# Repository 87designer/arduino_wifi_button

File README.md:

<!-- PROJECT LOGO -->
<br />
<div align="center">

  <p align="center">
    <br />
    <!-- <a href="https://github.com/87designer/arduino_infant_tracker"><strong>Explore the docs »</strong></a>
    <br />
    <br />
    <a href="https://github.com/87designer/arduino_infant_tracker">View Demo</a> -->
  </p>
</div>

<!-- TABLE OF CONTENTS -->
<details>
  <summary>Table of Contents</summary>
  <ol>
    <li>
      <a href="#about-the-project">About The Project</a>
      <ul>
        <li><a href="#built-with">Built With</a></li>
      </ul>
    </li>
    <li>
      <a href="#getting-started">Getting Started</a>
      <ul>
        <li><a href="#prerequisites">Prerequisites</a></li>
        <li><a href="#installation">Installation</a></li>
      </ul>
    </li>
    <li><a href="#usage">Usage</a></li>
    <li><a href="#roadmap">Roadmap</a></li>
    <li><a href="#acknowledgments">Acknowledgments</a></li>
  </ol>
</details>

<!-- ABOUT THE PROJECT -->
## About The Project

After being introduced to Arduino and electronics through the "30 Days Lost in Space" Adventure Kit from Inventr, I was served a social media ad for a small consumer button device that logged events to a dashboard, via wifi. Seeing how I could potentially leverage a device like this in my day to day, my gears got to turning.

```
Arduino + New Electronic Skills = I can make that
```

And with that, the AWB0412 categorical data logging wifi button was born. *(as an Arduino Uno Shield)*

When the device is powered on the LED in the top left will be red. After successful network connectino has been made, the LED will turn Green. When a Button is pressed the LED will blink blue.

There are 4 buttons on the shield giving the ability to log up to 12 different types of events using the methods of single click, double click, & hold +1 second for each button.

<br>
<hr>

#### 3D Model with Components *(Designed using KiCad)*

<div style="display:flex">
     <div style="flex:1;padding-right:10px;">
          
     </div>
     <div style="flex:1;padding-left:10px;">
          
     </div>
</div>

<br>
<hr>

#### PCB *(Vendor Mockup from Gerber files)*

<div style="display:flex">
     <div style="flex:1;padding-right:10px;">
          
     </div>
</div>

<p align="right">(<a href="#readme-top">back to top</a>)</p>

### Built With

* [![Arduino][Arduino]][Arduino-url]
* [![C++][Cplusplus]][Cplusplus-url]
* [![Kicad][KiCad]][KiCad-url]
* [![Google Sheets][googlesheets]][googlesheets-url]
* [![Google Apps Script][appsscript]][appsscript-url]

<p align="right">(<a href="#readme-top">back to top</a>)</p>

<!-- GETTING STARTED -->
## Getting Started

### Prerequisites

1) Install the [Arudino IDE](https://www.arduino.cc/en/software) on your computer
2) Install appropriate [Drivers](https://inventr.io/drivers/) for the Hero board
3) Install [ESP Libraries](https://github.com/esp8266/Arduino)
4) [Configure Cloud](https://www.youtube.com/watch?v=fS0GeaOkNRw) storage and app
    - Setup a Google Sheet to accept the timestamps and categories.
    - Deploy Google Apps Script code to listen for category request and write it to the google sheet.

### Materials:
  * 1 x [Arduino Hero](https://github.com/inventrkits/HERO)
  * 1 x A-Male to B-Male USB Cable
  * 1 x [ESP8266](https://en.wikipedia.org/wiki/ESP8266) ESP-01 Wifi Module
  * 1 x AWB-0412 Arduino Uno Shield PCB
  * 1 x Pin Headers (1x10)
  * 2 x Pin Headers (1x08)
  * 1 x Pin Headers (1x06)
  * 4 x 10ohm Resistor
  * 3 x 220ohm Resistor
  * 1 x RGB LED
  * 4 x 12mm Tactile Button
  * 1 x [EG1271](https://www.digikey.com/en/products/detail/e-switch/EG1271/251335) DPDT Switch Slide
  * 1 x [78B02ST](https://www.digikey.com/en/products/detail/grayhill-inc/78B02ST/726238) DIP Switch Slide

### Installation

<!-- Write about install/uploading the code for hero & wifi module-->

After construction of the Shield is complete, mount the shield to the Arduino and connect to your computer using the compatible USB cable to power on.

1. Open up the Arduino IDE and ensure the correct Board and Port are selected.
2. With all switches on the shield in the operating position, upload a [blank sketch]() to the Arduino.
3. Power down / disconnect the USB cable and slide DPDT switch and top DIP switch *(this will enable programming mode for the wifi module when powered is restored)*.
5. Reconnect the USB and change the board assignment in the IDE to the ESP8266 wifi module *(the port should be the same so ensure it is still assigned)*
6. Upload the [wifi sketch]() to the ESP8266.
7. Once the sketch is finished uploading, slide the top DIP switch on and off to reset the wifi module.
8. Power down / disconnect the USB cable and return all switches to operating position.
9. Reconnect the USB and change the board assignment in the IDE back to the Arduino.
10. Upload the [button sketch]() to the Arduino.
11. Once the sketch is finished uploading, power down / disconnect the USB cable from the computer and the device is ready to operate from an appropriate power source (battery, wall plug, usb cable.)

<p align="right">(<a href="#readme-top">back to top</a>)</p>

<!-- USAGE EXAMPLES -->
## Usage

#### Infant Tracker

One usage example of the AWB0412 wifi button shield would be as an Infant Tracker to help sleep deprived parents keep track of diapers, feedings, sleep schedule etc.

<p align="right">(<a href="#readme-top">back to top</a>)</p>

<!-- ROADMAP -->
## Roadmap

- [x] Breadboard Prototype to test functionality<br>
  
- [x] Document Prototype in hobby CAD software (Tinkercad / Fritzing)<br>
  
- [x] Electronic Design Automation (EDA), and 
    - [x] Schematic Capture<br>
      
    - [x] PCB Layout with Gerber output<br>
      <div style="display:flex">
        <div style="flex:1;padding-right:10px;">
          
        </div>
        <div style="flex:1;padding-right:10px;">
          
        </div>
      </div>
- [ ] Develop Final button commands
- [ ] Develop Method of Powering Device
- [ ] Draft Documentation
- [ ] Assemble Shield & Test Hardware
- [ ] Finalize Documentation
- [ ] Design / Fabricate a Housing possibly 3D printed model

<p align="right">(<a href="#readme-top">back to top</a>)</p>

<!-- ACKNOWLEDGMENTS -->
## Acknowledgments

* Special shoutout to the [Inventr](https://inventr.io/) Adventure Kit for laying the foundation for electronics that helped bring this project to life.
* [LogMaker360](https://www.youtube.com/watch?v=fS0GeaOkNRw) Youtube video walkthrough on how to get arduino to write to google sheets.
* [Electronics Hub](https://www.electronicshub.org/esp8266-arduino-interface/) Great article with detailed information regarding the ESP8266 ESP-01
* [Gerber/Drill File Generation Guide](https://support.jlcpcb.com/article/194-how-to-generate-gerber-and-drill-files-in-kicad-6) for PCB production at JLCPCB when using KiCad 6
* [Best-README-Template](https://github.com/othneildrew/Best-README-Template)

<p align="right">(<a href="#readme-top">back to top</a>)</p>

<!-- MARKDOWN LINKS & IMAGES -->
<!-- https://www.markdownguide.org/basic-syntax/#reference-style-links -->
[Arduino]: https://img.shields.io/badge/arduino-00979D?style=for-the-badge&logo=arduino&logoColor=white
[Arduino-url]: https://www.arduino.cc/
[Cplusplus]: https://img.shields.io/badge/C++-00599C?style=for-the-badge&logo=cplusplus&logoColor=white
[Cplusplus-url]: https://en.wikipedia.org/wiki/C%2B%2B
[KiCad]: https://img.shields.io/badge/KiCad-314CB0?style=for-the-badge&logo=kicad&logoColor=white
[KiCad-url]: https://www.kicad.org/
[googlesheets]: https://img.shields.io/badge/Google%20Sheets-34A853?style=for-the-badge&logo=googlesheets&logoColor=white
[googlesheets-url]: https://www.google.com/sheets/about/
[appsscript]: https://img.shields.io/badge/Google%20Apps%20Script-4285F4?style=for-the-badge&logo=googledrive&logoColor=white
[appsscript-url]: https://www.google.com/script/start/

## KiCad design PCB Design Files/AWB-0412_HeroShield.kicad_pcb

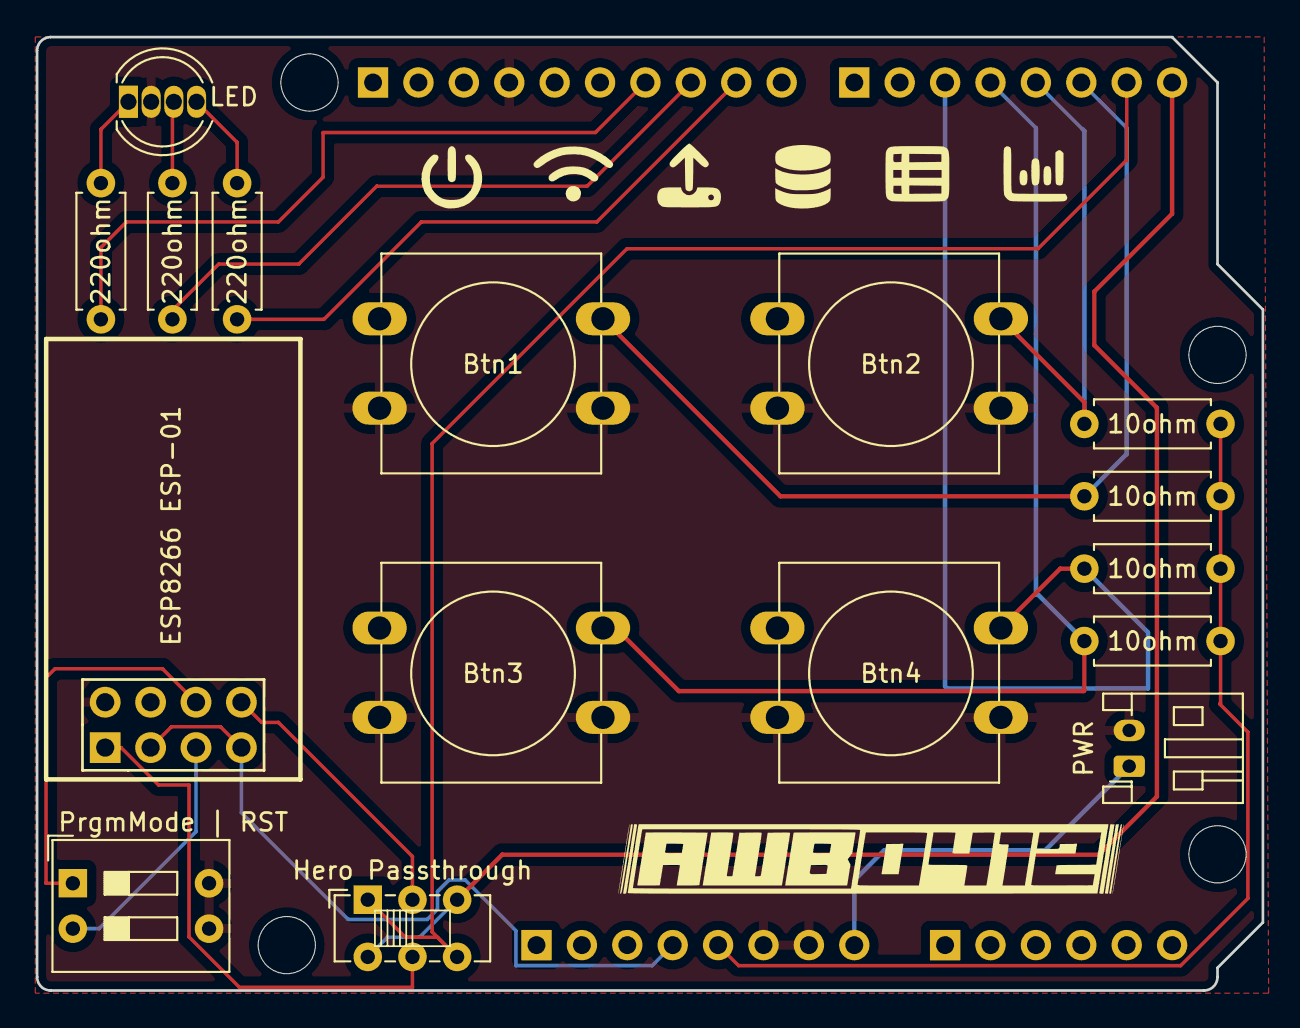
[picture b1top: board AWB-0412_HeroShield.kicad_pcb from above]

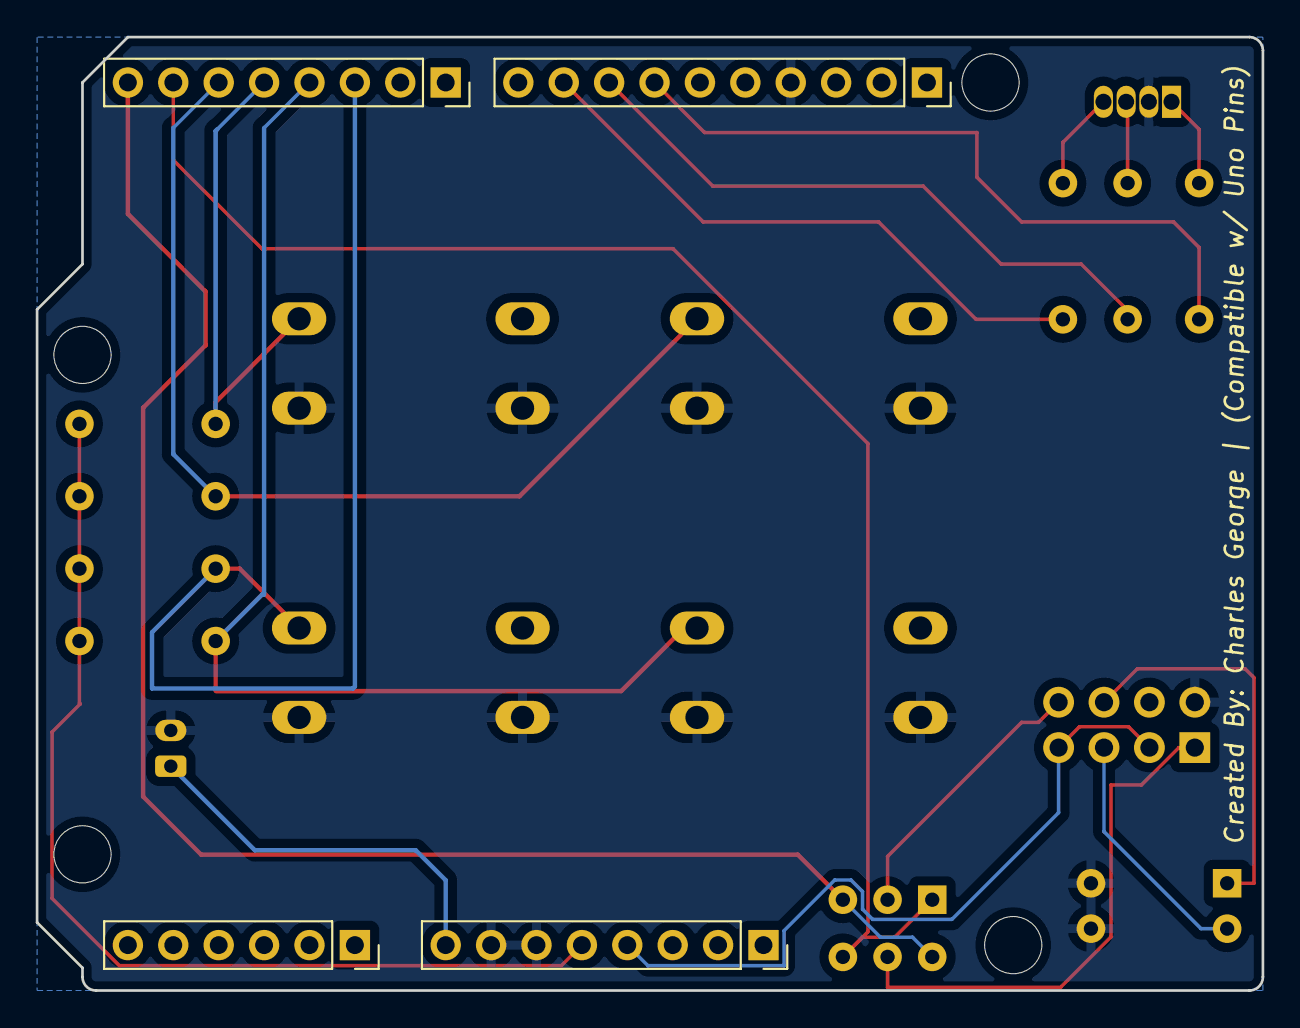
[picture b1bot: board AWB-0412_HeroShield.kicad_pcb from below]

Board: 2 copper layers, 68.6 x 53.3 mm, 24 parts (4 on the bottom side), 22 nets.

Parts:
10ohm, 10ohm#2, 10ohm#3, 10ohm#4, 220ohm, 220ohm#2, 220ohm#3: R; R_Axial_DIN0207_L6.3mm_D2.5mm_P7.62mm_Horizontal
Btn1, Btn2, Btn3, Btn4: SW_Push; SW_PUSH-12mm
ESP8266 ESP-01: ESP-01v090; ESP-01
Hero Passthrough: SW_Push_DPDT; SW_E-Switch_EG1271_SPDT
J1: Power; PinSocket_1x08_P2.54mm_Vertical
J2: Digital/PWM; PinSocket_1x10_P2.54mm_Vertical
J3: Analog; PinSocket_1x06_P2.54mm_Vertical
J4: Digital/PWM; PinSocket_1x08_P2.54mm_Vertical
LED: APA-106-F5; LED_D5.0mm-4_RGB
MH1, MH2, MH3, MH4: MountingHole_3.2mm
PWR: JST_PH_S2B-PH-K_1x02_P2.00mm_Horizontal
PrgmMode | RST: SW_DIP_x02; SW_DIP_SPSTx02_Slide_9.78x7.26mm_W7.62mm_P2.54mm

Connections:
+3V3: ESP8266 ESP-01.3 (CH_PD), ESP8266 ESP-01.7 (VCC), J1.4
+5V: 10ohm.2, 10ohm#2.2, 10ohm#3.2, 10ohm#4.2, J1.5
/2: 10ohm#3.1, Btn1.1, J4.6
/4: 10ohm.1, Btn3.1, J4.4
/*3: 10ohm#2.1, Btn2.1, J4.5
/*5: 10ohm#4.1, Btn4.1, J4.3
/*9: 220ohm#3.1, J2.9
/*10: 220ohm.1, J2.8
/*11: 220ohm#2.1, J2.7
/RX/0: Hero Passthrough.3 (C), Hero Passthrough.4 (A), J4.8
/SCL/A5: J2.1, J3.6
/SDA/A4: J2.2, J3.5
/TX/1: Hero Passthrough.1 (A), Hero Passthrough.6 (C), J4.7
GND: Btn1.2, Btn2.2, Btn3.2, Btn4.2, ESP8266 ESP-01.2 (GND), J1.6, J1.7, J2.4, LED.2 (GND), PWR.2, PrgmMode | RST.3, PrgmMode | RST.4
unnamed: 220ohm.2, LED.3 (VDD)
unnamed: 220ohm#3.2, LED.4 (DI)
unnamed: 220ohm#2.2, LED.1 (DO)
unnamed: ESP8266 ESP-01.8 (URXD), Hero Passthrough.2 (B)
unnamed: ESP8266 ESP-01.1 (UTXD), Hero Passthrough.5 (B)
unnamed: ESP8266 ESP-01.6 (GPIO0), PrgmMode | RST.1
unnamed: ESP8266 ESP-01.5 (RST), PrgmMode | RST.2
VCC: J1.8, PWR.1

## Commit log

2023-01-24 Update Draft README
2023-01-24 Added PCB images
2023-01-24 image name update
2023-01-25 Cleaner README Draft
2023-01-25 README Update
    Image Size Adjustments
2023-01-25 Update README
    Added Roadmap images
2023-01-25 Update README
    Line Return adjustment
2023-01-26 Add PCB files
2023-01-26 Add Arduino Sketch and Google App Script code
2023-01-26 Update to Component List
2023-01-29 Update PCB files
    Updated the PCB files. Altered LED connections to ensure analog out compatible pins were connected to the LED. As well as added a JST PH 2-Pin connector for providing power.
2023-01-30 Update Sketches
    Added Wifi Manager
2023-02-01 Update Wifi Sketch
